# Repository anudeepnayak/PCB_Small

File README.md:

# PCB_Small
Schematic and Layout for Dynamixel XL-320.

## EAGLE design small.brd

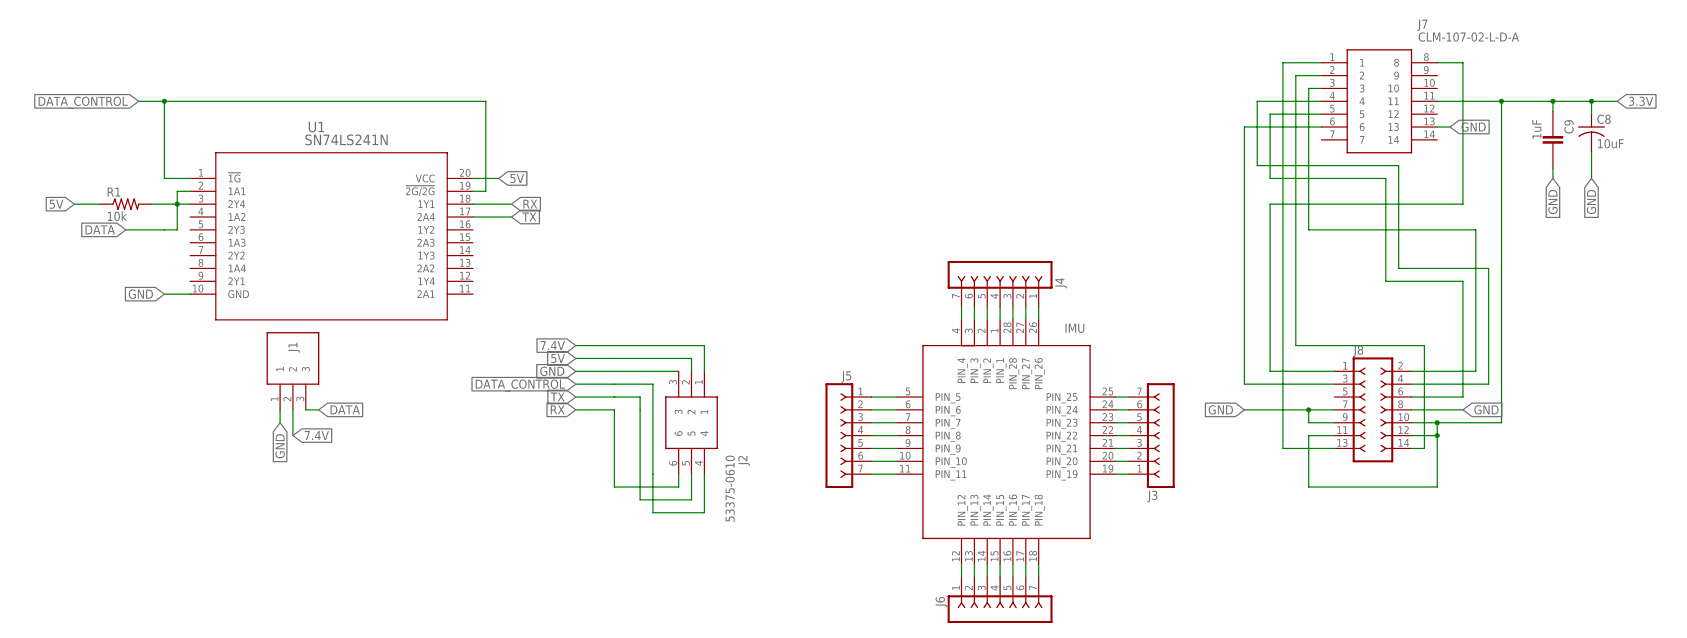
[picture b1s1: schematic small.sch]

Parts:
C8: 10uF; C0805; MPN 12063D106KAT2A
C9: 1uF; CC0603KRX7R9BB104_CAPC1608X90; MPN 08053C105KAT2A
J1: 53253-0370; SHDR3W50P0X200_1X3_800X365X570
J2: 53375-0610; MPN 53375-0610
J3, J4, J5, J6: F-1X07-SIP-100-32; SIP-100-07-32
J7: CLM-107-02-L-D-A; CLM10702LDA
J8: F-2X07-DIL-100; DIL-100-2X07
R1: 10k; M0805; MPN CRCW080510K0JNEA
U1: SN74LS241N; N20; MPN SN74LS241N
U$1: IMU; PLCC28S

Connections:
3.3V: C8.1, C9.1, J7.11, J8.10, J8.11, J8.12
5V: J2.2, R1.1, U1.20 (VCC)
7.4V: J1.2, J2.1
DATA: J1.3, R1.2, U1.2 (1A1), U1.3 (2Y4)
DATA_CONTROL: J2.4, U1.1 (!1G), U1.19 (!2G/2G)
GND: C8.2, C9.2, J1.1, J2.3, J7.13, J8.7, J8.8, J8.9, U1.10 (GND)
unnamed: J4.7, U$1.4 (PIN_4)
unnamed: J4.6, U$1.3 (PIN_3)
unnamed: J4.5, U$1.2 (PIN_2)
unnamed: J4.4, U$1.1 (PIN_1)
unnamed: J4.3, U$1.28 (PIN_28)
unnamed: J4.2, U$1.27 (PIN_27)
unnamed: J4.1, U$1.26 (PIN_26)
unnamed: J3.7, U$1.25 (PIN_25)
unnamed: J3.6, U$1.24 (PIN_24)
unnamed: J3.5, U$1.23 (PIN_23)
unnamed: J3.4, U$1.22 (PIN_22)
unnamed: J3.3, U$1.21 (PIN_21)
unnamed: J3.2, U$1.20 (PIN_20)
unnamed: J3.1, U$1.19 (PIN_19)
unnamed: J6.7, U$1.18 (PIN_18)
unnamed: J6.6, U$1.17 (PIN_17)
unnamed: J6.5, U$1.16 (PIN_16)
unnamed: J6.4, U$1.15 (PIN_15)
unnamed: J6.3, U$1.14 (PIN_14)
unnamed: J6.2, U$1.13 (PIN_13)
unnamed: J6.1, U$1.12 (PIN_12)
unnamed: J5.7, U$1.11 (PIN_11)
unnamed: J5.6, U$1.10 (PIN_10)
unnamed: J5.5, U$1.9 (PIN_9)
unnamed: J5.4, U$1.8 (PIN_8)
unnamed: J5.3, U$1.7 (PIN_7)
unnamed: J5.2, U$1.6 (PIN_6)
unnamed: J5.1, U$1.5 (PIN_5)
unnamed: J7.1, J8.13
unnamed: J7.2, J8.14
unnamed: J7.3, J8.2
unnamed: J7.4, J8.4
unnamed: J7.5, J8.6
unnamed: J7.8, J8.1
unnamed: J7.6, J8.3
RX: J2.6, U1.18 (1Y1)
TX: J2.5, U1.17 (2A4)

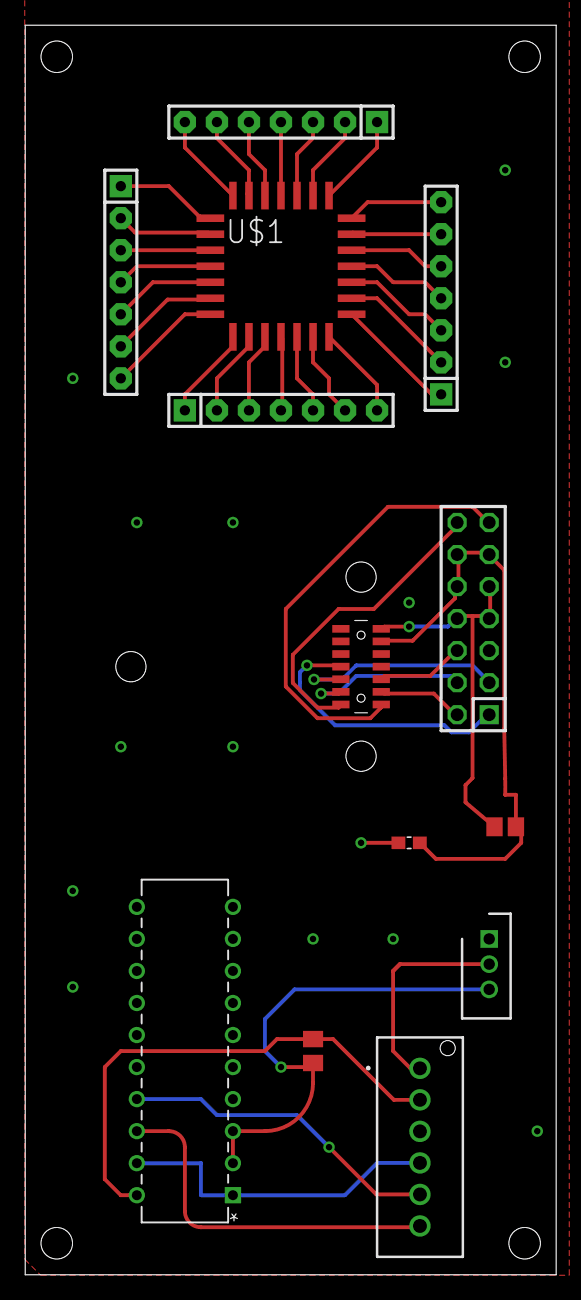
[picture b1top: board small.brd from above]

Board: 2 copper layers, 42.1 x 99.1 mm, 13 parts (0 on the bottom side), 43 nets.

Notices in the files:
parts and their libraries:
con-headers-jp: Copyright (C) 2008, Bob Starr
